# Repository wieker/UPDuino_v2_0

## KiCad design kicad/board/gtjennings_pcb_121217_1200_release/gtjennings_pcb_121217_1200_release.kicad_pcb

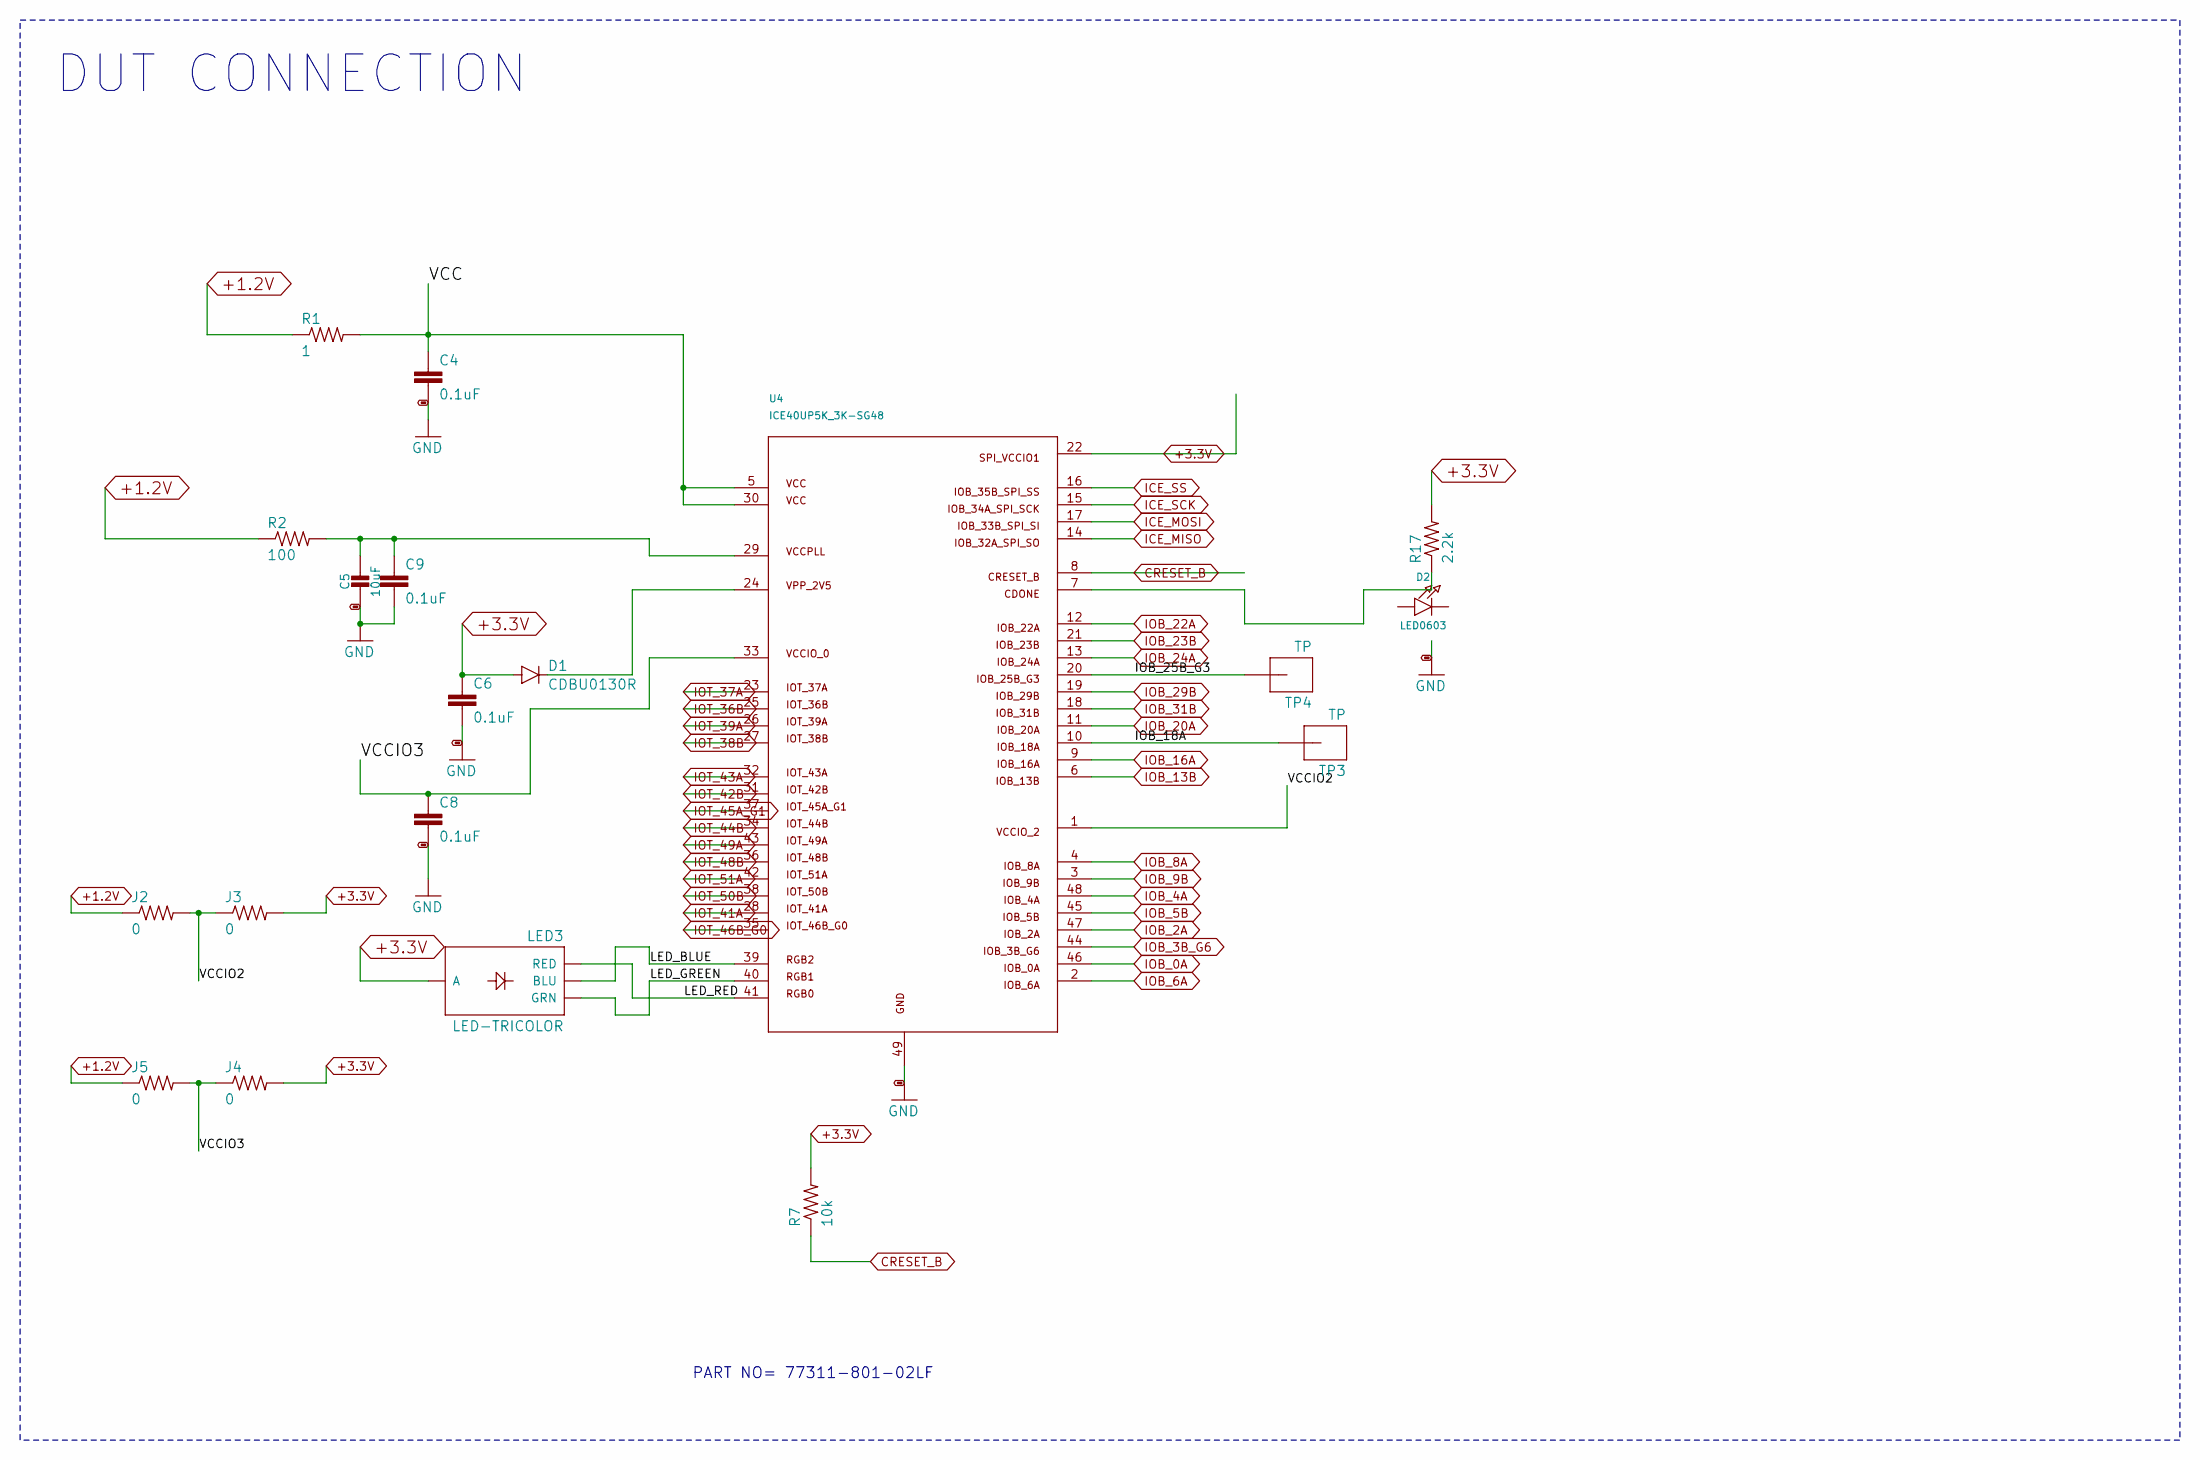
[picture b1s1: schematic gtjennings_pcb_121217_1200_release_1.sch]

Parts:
C4, C6, C8, C9: 0.1uF; 0603-CAP
C5: 10uF; 0603-NO
D1: CDBU0130R; SOD523
D2: LED0603; LED-0603
J2, J3, J4, J5: 0; 0603-RES
LED: LED-TRICOLOR; LED-TRICOLOR-SMD
R1: 1; 0603-RES
R2: 100; 0603-RES
R7: 10k; 0603-RES
R17: 2.2k; 0603-RES
TP3, TP4: TP
U4: ICE40UP5K_3K-SG48

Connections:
+1.2V: J2.1, J5.1, R1.1, R2.1; also elsewhere on the board
+3.3V: C6.1, D1.A, J3.2, J4.2, R7.2, R17.2, U4.22; also elsewhere on the board
/gtjennings_pcb_121217_1200_release_1/IOB_18A: TP3.1, U4.10
/gtjennings_pcb_121217_1200_release_1/IOB_25B_G3: TP4.1, U4.20
/gtjennings_pcb_121217_1200_release_1/LED_BLUE: U4.39; also elsewhere on the board
/gtjennings_pcb_121217_1200_release_1/LED_GREEN: U4.40; also elsewhere on the board
/gtjennings_pcb_121217_1200_release_1/LED_RED: U4.41; also elsewhere on the board
/gtjennings_pcb_121217_1200_release_1/VCC: C4.1, R1.2, U4.5, U4.30
/gtjennings_pcb_121217_1200_release_1/VCCIO2: J2.2, J3.1, U4.1
/gtjennings_pcb_121217_1200_release_1/VCCIO3: C8.1, J4.1, J5.2, U4.33
CRESET_B: R7.1, U4.8; also elsewhere on the board
GND: C4.2, C5.2, C6.2, C8.2, C9.2, U4.49; also elsewhere on the board
ICE_MISO: U4.14; also elsewhere on the board
ICE_MOSI: U4.17; also elsewhere on the board
ICE_SCK: U4.15; also elsewhere on the board
ICE_SS: U4.16; also elsewhere on the board
IOB_0A: U4.46; also elsewhere on the board
IOB_2A: U4.47; also elsewhere on the board
IOB_3B_G6: U4.44; also elsewhere on the board
IOB_4A: U4.48; also elsewhere on the board
IOB_5B: U4.45; also elsewhere on the board
IOB_6A: U4.2; also elsewhere on the board
IOB_8A: U4.4; also elsewhere on the board
IOB_9B: U4.3; also elsewhere on the board
IOB_13B: U4.6; also elsewhere on the board
IOB_16A: U4.9; also elsewhere on the board
IOB_20A: U4.11; also elsewhere on the board
IOB_22A: U4.12; also elsewhere on the board
IOB_23B: U4.21; also elsewhere on the board
IOB_24A: U4.13; also elsewhere on the board
IOB_29B: U4.19; also elsewhere on the board
IOB_31B: U4.18; also elsewhere on the board
IOT_36B: U4.25; also elsewhere on the board
IOT_37A: U4.23; also elsewhere on the board
IOT_38B: U4.27; also elsewhere on the board
IOT_39A: U4.26; also elsewhere on the board
IOT_41A: U4.28; also elsewhere on the board
IOT_42B: U4.31; also elsewhere on the board
IOT_43A: U4.32; also elsewhere on the board
IOT_44B: U4.34; also elsewhere on the board
IOT_45A_G1: U4.37; also elsewhere on the board
IOT_46B_G0: U4.35; also elsewhere on the board
IOT_48B: U4.36; also elsewhere on the board
IOT_49A: U4.43; also elsewhere on the board
IOT_50B: U4.38; also elsewhere on the board
IOT_51A: U4.42; also elsewhere on the board
unnamed: C5.1, C9.1, R2.2, U4.29
unnamed: D1.C, U4.24
unnamed: R17.1, U4.7

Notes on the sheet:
DUT CONNECTION
PART NO= 77311-801-02LF

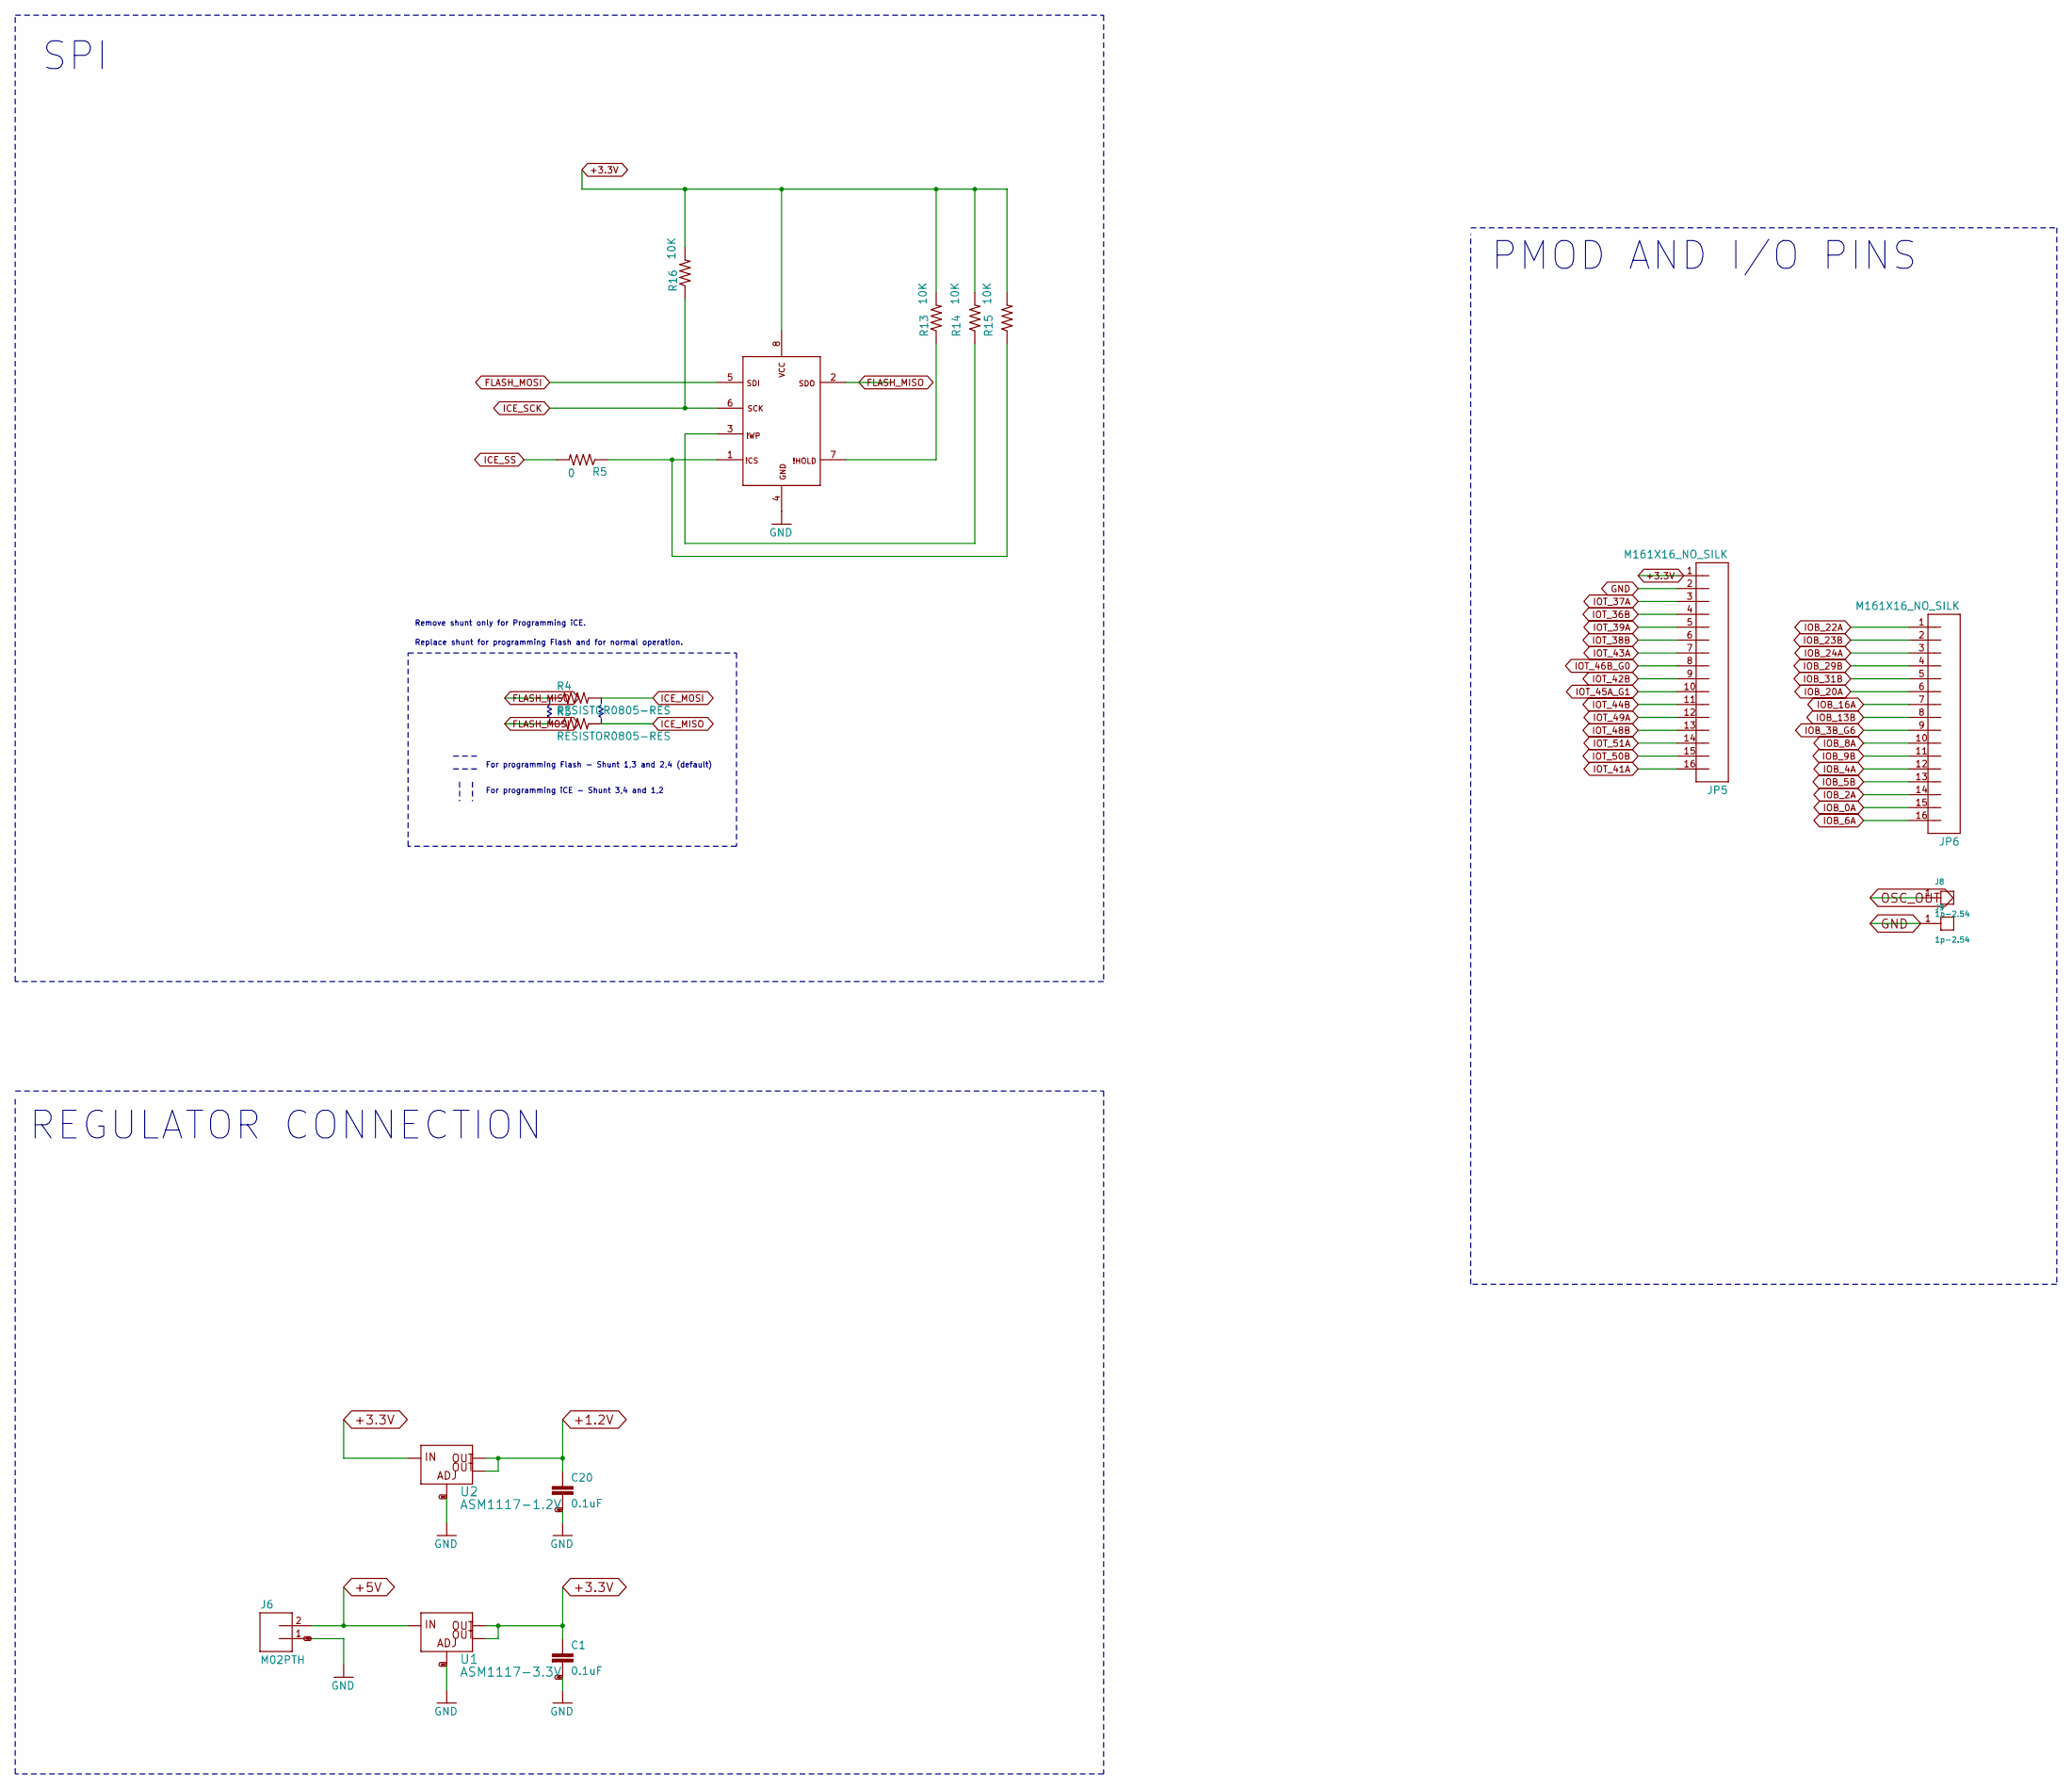
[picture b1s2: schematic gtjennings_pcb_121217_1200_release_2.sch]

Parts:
C1, C20: 0.1uF; 0603-CAP
J6: M02PTH; 1X02
J8, J9: 1p-2.54; 1P-65_35MIL
JP5, JP6: M161X16_NO_SILK; 1X16_NO_SILK
R3, R4: RESISTOR0805-RES; 0805
R5: 0; 0805
R13, R14, R15, R16: 10K; 0603-RES
U1: ASM1117-3.3V; SOT223
U2: ASM1117-1.2V; SOT223
U3: N25Q032A13ESC40F-ND; SO8

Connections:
+1.2V: C20.1, U2.2 (OUT), U2.4 (OUT@1); also elsewhere on the board
+3.3V: C1.1, JP5.1, R13.2, R14.2, R15.2, R16.2, U1.2 (OUT), U1.4 (OUT@1), U2.3 (IN), U3.8; also elsewhere on the board
+5V: J6.2, U1.3 (IN); also elsewhere on the board
FLASH_MISO: R4.1, U3.2; also elsewhere on the board
FLASH_MOSI: R3.1, U3.5; also elsewhere on the board
GND: C1.2, C20.2, J6.1, J9.1, JP5.2, U1.1 (ADJ), U2.1 (ADJ), U3.4; also elsewhere on the board
ICE_MISO: R3.2; also elsewhere on the board
ICE_MOSI: R4.2; also elsewhere on the board
ICE_SCK: R16.1, U3.6; also elsewhere on the board
ICE_SS: R5.2; also elsewhere on the board
IOB_0A: JP6.15; also elsewhere on the board
IOB_2A: JP6.14; also elsewhere on the board
IOB_3B_G6: JP6.9; also elsewhere on the board
IOB_4A: JP6.12; also elsewhere on the board
IOB_5B: JP6.13; also elsewhere on the board
IOB_6A: JP6.16; also elsewhere on the board
IOB_8A: JP6.10; also elsewhere on the board
IOB_9B: JP6.11; also elsewhere on the board
IOB_13B: JP6.8; also elsewhere on the board
IOB_16A: JP6.7; also elsewhere on the board
IOB_20A: JP6.6; also elsewhere on the board
IOB_22A: JP6.1; also elsewhere on the board
IOB_23B: JP6.2; also elsewhere on the board
IOB_24A: JP6.3; also elsewhere on the board
IOB_29B: JP6.4; also elsewhere on the board
IOB_31B: JP6.5; also elsewhere on the board
IOT_36B: JP5.4; also elsewhere on the board
IOT_37A: JP5.3; also elsewhere on the board
IOT_38B: JP5.6; also elsewhere on the board
IOT_39A: JP5.5; also elsewhere on the board
IOT_41A: JP5.16; also elsewhere on the board
IOT_42B: JP5.9; also elsewhere on the board
IOT_43A: JP5.7; also elsewhere on the board
IOT_44B: JP5.11; also elsewhere on the board
IOT_45A_G1: JP5.10; also elsewhere on the board
IOT_46B_G0: JP5.8; also elsewhere on the board
IOT_48B: JP5.13; also elsewhere on the board
IOT_49A: JP5.12; also elsewhere on the board
IOT_50B: JP5.15; also elsewhere on the board
IOT_51A: JP5.14; also elsewhere on the board
unnamed: R13.1, U3.7
unnamed: R14.1, U3.3
unnamed: R5.1, R15.1, U3.1
OSC_OUT: J8.1; also elsewhere on the board

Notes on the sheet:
For programming Flash - Shunt 1,3 and 2,4 (default)
For programming iCE - Shunt 3,4 and 1,2
Remove shunt only for Programming iCE.
Replace shunt for programming Flash and for normal operation.
SPI
REGULATOR CONNECTION
PMOD AND I/O PINS

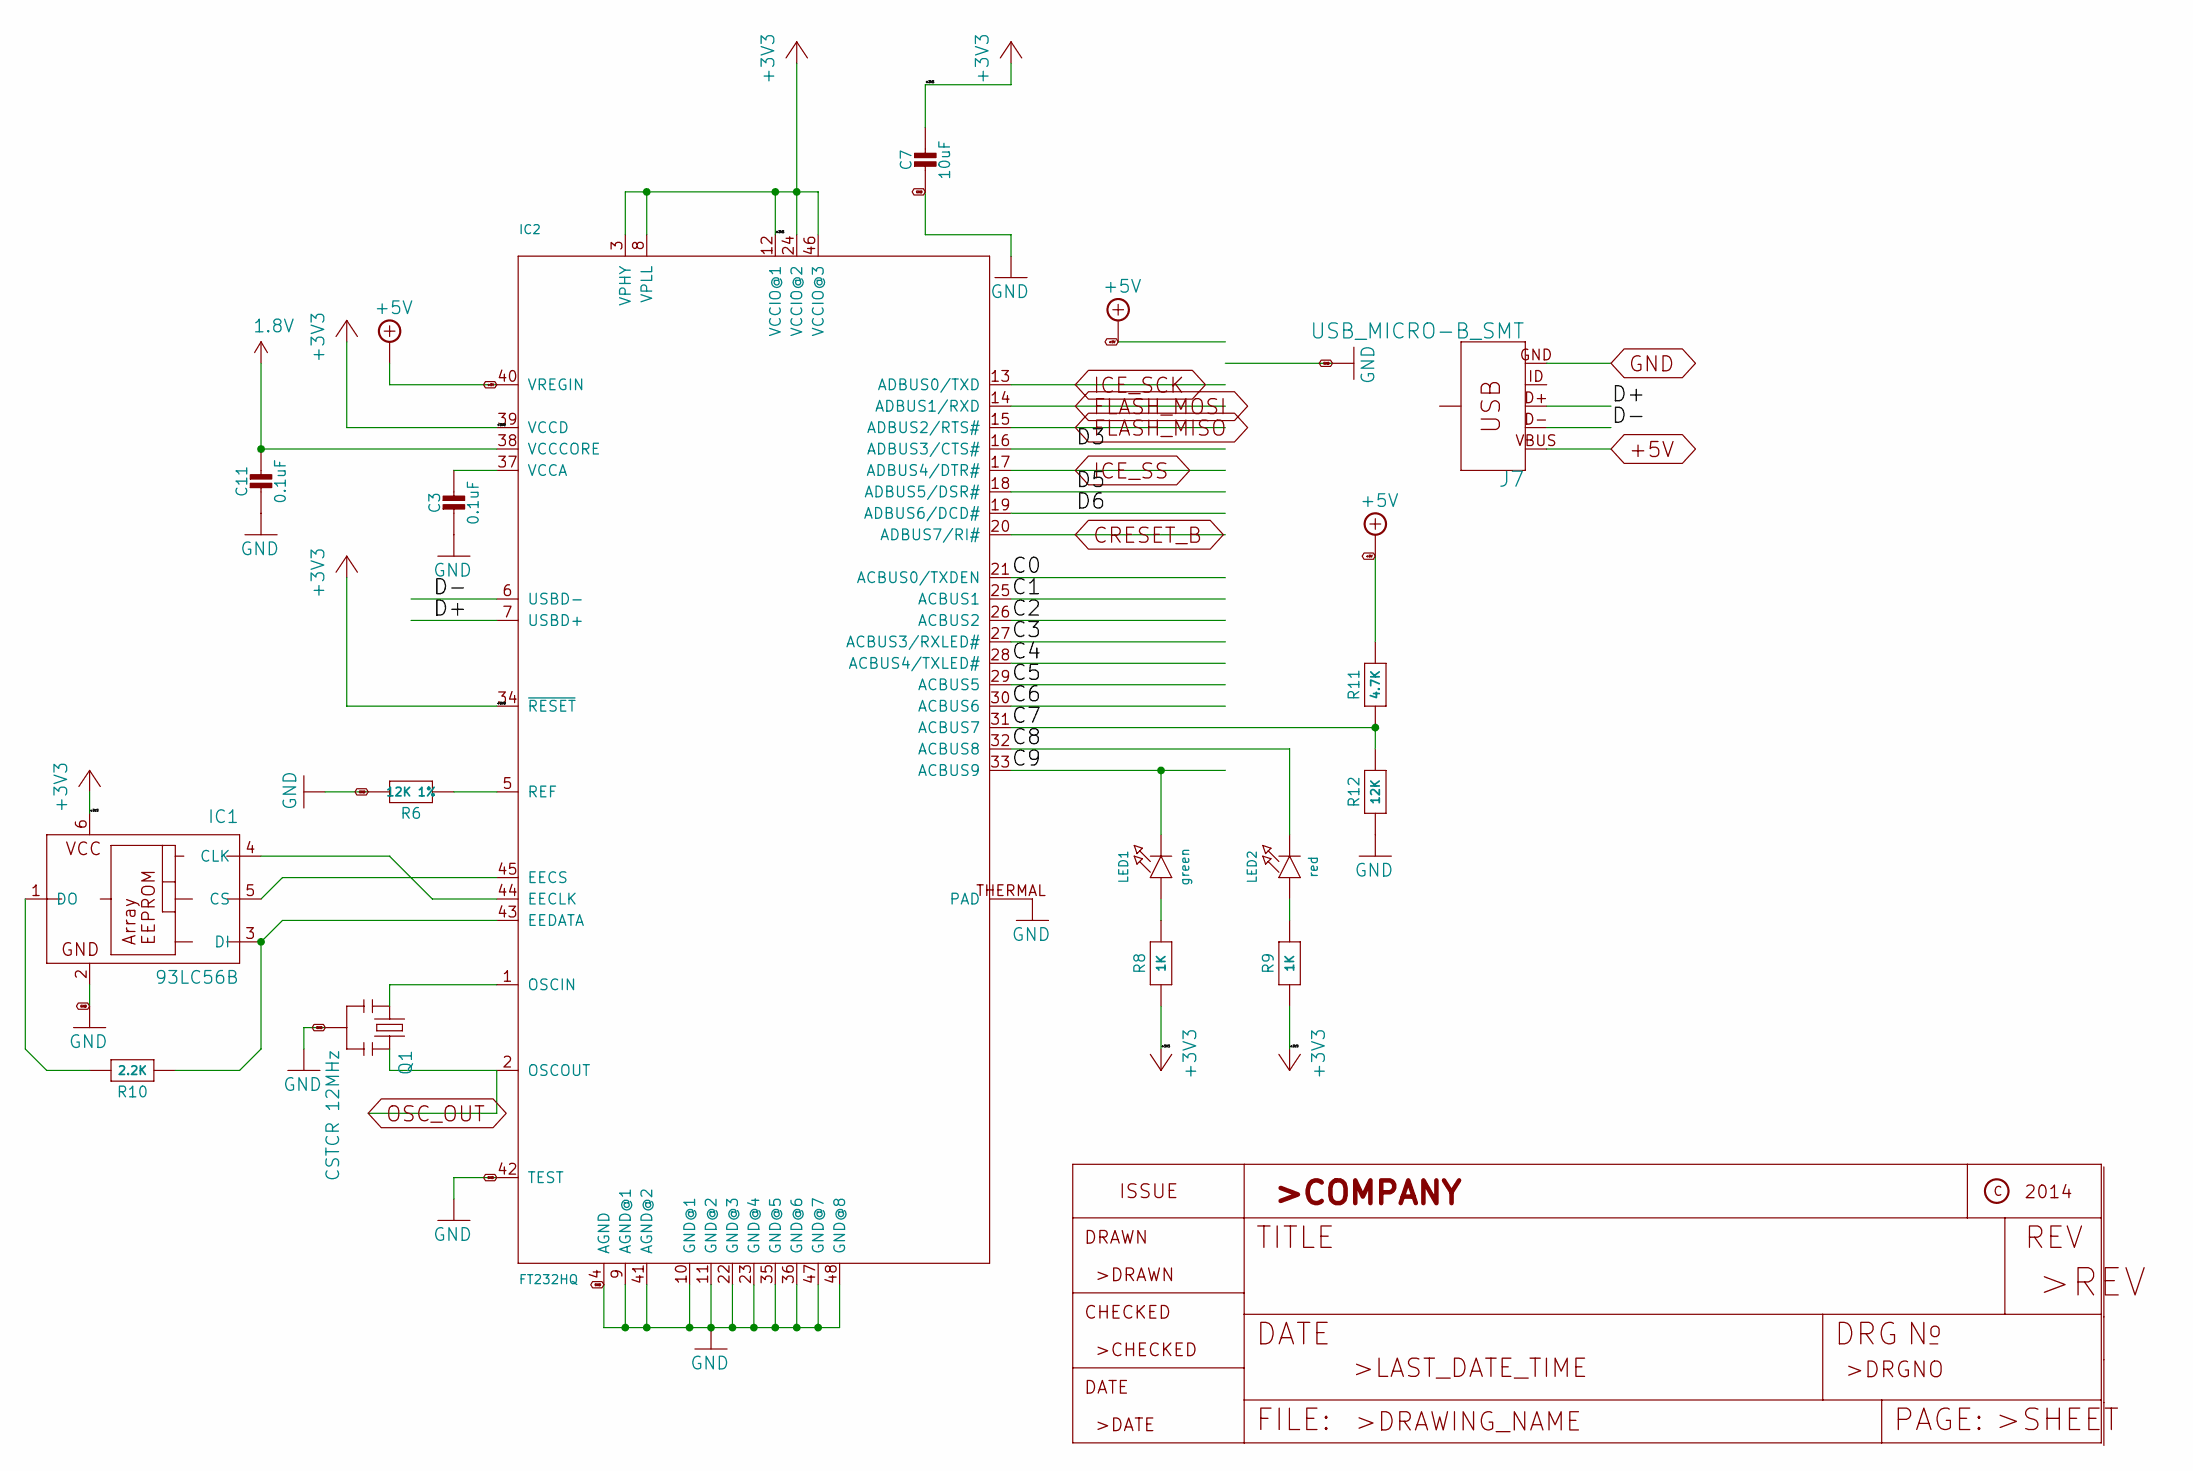
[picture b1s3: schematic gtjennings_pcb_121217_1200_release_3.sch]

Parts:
C3: 0.1uF; 0603-NO
C7: 10uF; 0603-NO
C11: 0.1uF; 0603-MINI
IC1: 93LC56B; SOT23-6
IC2: FT232HQ; QFN48_8MM
J7: USB_MICRO-B_SMT; USB-MICROB
LED1: green; CHIPLED_0805_NOOUTLINE
LED2: red; CHIPLED_0805_NOOUTLINE
Q1: CSTCR 12MHz; RESONATOR-SMD
R6: 12K 1%; _0603
R8, R9: 1K; 0603-MINI
R10: 2.2K; _0805MP
R11: 4.7K; 0603-MINI
R12: 12K; 0603-MINI

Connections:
1.8V: C11.1, IC2.38 (VCCCORE)
+3V3: C7.1, IC1.6 (VCC), IC2.3 (VPHY), IC2.8 (VPLL), IC2.12 (VCCIO@1), IC2.24 (VCCIO@2), IC2.34 (~RESET), IC2.39 (VCCD), IC2.46 (VCCIO@3), R8.1, R9.1
+5V: IC2.40 (VREGIN), J7.VBUS, R11.2; also elsewhere on the board
/gtjennings_pcb_121217_1200_release_3/C0: IC2.21 (ACBUS0/TXDEN)
/gtjennings_pcb_121217_1200_release_3/C1: IC2.25 (ACBUS1)
/gtjennings_pcb_121217_1200_release_3/C2: IC2.26 (ACBUS2)
/gtjennings_pcb_121217_1200_release_3/C3: IC2.27 (ACBUS3/RXLED#)
/gtjennings_pcb_121217_1200_release_3/C4: IC2.28 (ACBUS4/TXLED#)
/gtjennings_pcb_121217_1200_release_3/C5: IC2.29 (ACBUS5)
/gtjennings_pcb_121217_1200_release_3/C6: IC2.30 (ACBUS6)
/gtjennings_pcb_121217_1200_release_3/C7: IC2.31 (ACBUS7), R11.1, R12.2
/gtjennings_pcb_121217_1200_release_3/C8: IC2.32 (ACBUS8), LED2.C
/gtjennings_pcb_121217_1200_release_3/C9: IC2.33 (ACBUS9), LED1.C
/gtjennings_pcb_121217_1200_release_3/D3: IC2.16 (ADBUS3/CTS#)
/gtjennings_pcb_121217_1200_release_3/D5: IC2.18 (ADBUS5/DSR#)
/gtjennings_pcb_121217_1200_release_3/D6: IC2.19 (ADBUS6/DCD#)
/gtjennings_pcb_121217_1200_release_3/D+: IC2.7 (USBD+), J7.D+
/gtjennings_pcb_121217_1200_release_3/D-: IC2.6 (USBD-), J7.D-
CRESET_B: IC2.20 (ADBUS7/RI#); also elsewhere on the board
FLASH_MISO: IC2.15 (ADBUS2/RTS#); also elsewhere on the board
FLASH_MOSI: IC2.14 (ADBUS1/RXD); also elsewhere on the board
GND: C3.2, C7.2, C11.2, IC1.2 (GND), IC2.4 (AGND), IC2.9 (AGND@1), IC2.10 (GND@1), IC2.11 (GND@2), IC2.22 (GND@3), IC2.23 (GND@4), IC2.35 (GND@5), IC2.36 (GND@6), IC2.41 (AGND@2), IC2.42 (TEST), IC2.47 (GND@7), IC2.48 (GND@8), IC2.THERMAL (PAD), J7.GND, Q1.2, R6.2, R12.1; also elsewhere on the board
ICE_SCK: IC2.13 (ADBUS0/TXD); also elsewhere on the board
ICE_SS: IC2.17 (ADBUS4/DTR#); also elsewhere on the board
unnamed: C3.1, IC2.37 (VCCA)
unnamed: IC1.1 (DO), R10.2
unnamed: IC1.3 (DI), IC2.43 (EEDATA), R10.1
unnamed: IC1.4 (CLK), IC2.44 (EECLK)
unnamed: IC1.5 (CS), IC2.45 (EECS)
unnamed: IC2.1 (OSCIN), Q1.1
unnamed: IC2.5 (REF), R6.1
unnamed: J7.MT1 (SHIELD), J7.MT2 (SHIELD), J7.P$1 (SHIELD), J7.P$2 (SHIELD)
unnamed: LED1.A, R8.2
unnamed: LED2.A, R9.2
OSC_OUT: IC2.2 (OSCOUT), Q1.3; also elsewhere on the board

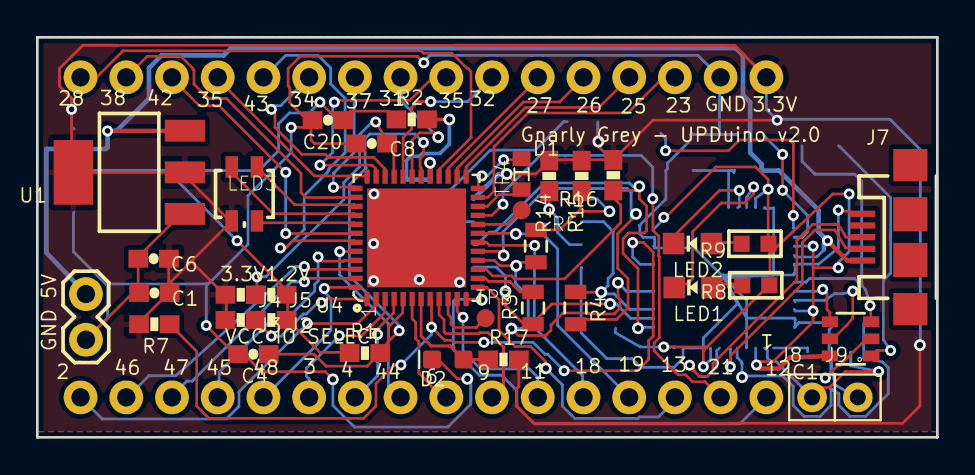
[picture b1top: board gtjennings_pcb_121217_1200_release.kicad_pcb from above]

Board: 2 copper layers, 50.0 x 22.2 mm, 51 parts (0 on the bottom side), 73 nets.

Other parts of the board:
LED3: LED-TRICOLOR; LED-TRICOLOR-SMD

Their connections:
+3.3V: LED3.A; also elsewhere on the board
/gtjennings_pcb_121217_1200_release_1/LED_BLUE: LED3.B; also elsewhere on the board
/gtjennings_pcb_121217_1200_release_1/LED_GREEN: LED3.G; also elsewhere on the board
/gtjennings_pcb_121217_1200_release_1/LED_RED: LED3.R; also elsewhere on the board

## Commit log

2019-05-26 kicad import
